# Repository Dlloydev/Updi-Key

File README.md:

# Updi-Key

#### What is it?

Updi-Key is an inline adapter that transforms your favorite UPDI programmer into a HV UPDI programmer.  Now you can easily enable UPDI mode, program and power-cycle your target MCU to explore additional features like using the UPDI pin for LUT0, AIN0, GPIO or Reset.

#### Why did you make it?

To provide a tool that allows easy access to the additional functions of the programming pin, which becomes more important in low pin count applications. To enhance your existing programming solution with a convenient low cost adapter.

#### What makes it special?

Unique, versatile, easy to use with the existing programming environment you're already familiar with.

- Converts any UPDI programmer to HV-UPDI
- Connects directly in-line with the MPLAB Snap In-Circuit Debugger (pins 2, 3, 4)
- Connects directly in-line with many ATtiny 0/1/2 development and breakout boards
- Provides standard 6-pin UPDI headers with pin 3 used for additional functions
- The 3-pin UPDI headers can be any combination of male/female or vertical/horizontal at each end
- Automatically provides target power-cycle with current limiting protection
- Directly compatible with any target voltage from 3V to 5V without reprogramming the device
- Host UPDI is inherently protected by using "break-before-make" signal transfer
- No power hungry resistor-diode host UPDI protection circuit required
- Built-in low noise, low EMI, low power 3-5VDC to 12VDC converter (25mA) 
-  Fast HV pulse timing similar to the Atmel Power Debugger
- Continuously monitors host UPDI signal and Re-Updify button on one pin for detecting stable or busy status of the UPDI signal and pushbutton status 
- Green VTG-PC status LED and Orange HV pulse LED
- It seems fitting that the smallest MCU in the family (ATtiny202) operates the key

#### Updi-Key Digi-Key BOM

| Item | Qty  | Reference   | Manufacturer  Number                                         | Digi-Key Part Number     | Description                                                |
| ---- | ---- | ----------- | ------------------------------------------------------------ | ------------------------ | ---------------------------------------------------------- |
| 1    | 3    | C1, C7, C8  | [CL10B104KB8NNNC](https://www.mouser.ca/datasheet/2/585/MLCC-1837944.pdf) | 1276-1000-1-ND           | CAP CER 0.1UF 50V X7R 0603                                 |
| 2    | 1    | C6          | [CL10A475KO8NNNC](https://media.digikey.com/pdf/Data%20Sheets/Samsung%20PDFs/CL10A475KO8NNNC_Spec.pdf) | 1276-1784-1-ND           | CAP CER 4.7UF 16V X5R 0603                                 |
| 3    | 1    | D2          | [PMEG4005CEJX](https://assets.nexperia.com/documents/data-sheet/PMEG4005CEJ.pdf) | 1727-8169-1-ND           | DIODE SCHOTTKY 40V 500MA SC90                              |
| 4    | 2    | R8, R9      | [RK73B1JTTD102J](http://www.koaspeer.com/pdfs/RK73B.pdf)     | 2019-RK73B1JTTD102JCT-ND | RES 1K OHM 5% 1/8W 0603                                    |
| 5    | 3    | R3, R4, R10 | [RK73B1JTTD103J](http://www.koaspeer.com/pdfs/RK73B.pdf)     | 2019-RK73B1JTTD103JCT-ND | RES 10K OHM 5% 1/10W 0603                                  |
| 6    | 2    | R11, R12    | [RK73B1JTTD181J](http://www.koaspeer.com/pdfs/RK73B.pdf)     | 2019-RK73B1JTTD181JCT-ND | RES 180 OHM 5% 1/8W 0603                                   |
| 7    | 1    | SW1         | [SN74LVC1G3157DBVR](http://www.ti.com/general/docs/suppproductinfo.tsp?distId=10&gotoUrl=http%3A%2F%2Fwww.ti.com%2Flit%2Fgpn%2Fsn74lvc1g3157) | 296-14908-1-ND           | IC SWITCH SPDT SOT23-6                                     |
| 8    | 1    | R6          | [RC0603FR-0711KL](https://www.yageo.com/upload/media/product/productsearch/datasheet/rchip/PYu-RC_Group_51_RoHS_L_11.pdf) | 311-11.0KHRCT-ND         | RES SMD 11K OHM 1% 1/10W 0603                              |
| 9    | 1    | R5          | [RC0603FR-07102KL](https://www.yageo.com/upload/media/product/productsearch/datasheet/rchip/PYu-RC_Group_51_RoHS_L_11.pdf) | 311-102KHRCT-ND          | RES SMD 102K OHM 1% 1/10W 0603                             |
| 10   | 1    | C4          | [CC0603BRNPO9BNR68](https://www.yageo.com/upload/media/product/productsearch/datasheet/mlcc/UPY-GP_NP0_16V-to-50V_18.pdf) | 311-3842-1-ND            | CAP CER 0.68PF 50V NPO 0603                                |
| 11   | 1    | VTG1        | [LG Q396-PS-35](https://dammedia.osram.info/media/resource/hires/osram-dam-2493948/LG%20Q396.pdf) | 475-3754-1-ND            | LED GREEN DIFFUSED 0603 SMD                                |
| 12   | 1    | F1          | [0ZCM0005FF2G](https://belfuse.com/resources/datasheets/circuitprotection/ds-cp-0zcm-series.pdf) | 507-1816-1-ND            | PTC RESET FUSE 15V 50MA 0603                               |
| 13   | 1    | U3          | [MIC2091-1YM5-TR](http://www.microchip.com/mymicrochip/filehandler.aspx?ddocname=en579481) | 576-3891-1-ND            | MICROCHIP - MIC2091-1YM5-TR - POWER SWITCH, 100MA, SOT23-5 |
| 14   | 1    | L1          | [CBC2518T470K](https://www.mouser.ca/datasheet/2/396/wound02_e-13113-1206718.pdf) | 587-3060-1-ND            | FIXED IND 47UH 290MA 2.47 OHM                              |
| 15   | 3    | C2, C3, C5  | [LMK107BBJ106MALT](https://www.mouser.ca/datasheet/2/396/wound02_e-13113-1206718.pdf) | 587-3258-1-ND            | CAP CER 10UF 10V X5R 0603                                  |
| 16   | 1    | HV1         | [APTD1608SECK/J4-PF](https://www.mouser.ca/datasheet/2/216/APTD1608SECK-J4-PF-472092.pdf) | 754-1802-1-ND            | LED ORANGE CLEAR 0603 (1608 Metric)                        |
| 17   | 1    | U1          | [ATTINY202-SSNR](http://ww1.microchip.com/downloads/en/DeviceDoc/ATtiny202-402-AVR-MCU-with-Core-Independent-Peripherals_and-picoPower-40001969A.pdf) | ATTINY202-SSNRCT-ND      | IC MCU 8BIT 2KB FLASH 8SOIC                                |
| 18   | 1    | SW3         | [PTS810SJG250SMTRLFS](https://dznh3ojzb2azq.cloudfront.net/products/Tactile/PTS810/documents/datasheet.pdf) | CKN10504CT-ND            | SWITCH TACTILE SPST-NO 0.05A 16V                           |
| 19   | 1    | SW2         | [ISL43210IHZ-T](https://www.renesas.com/en-us/www/doc/datasheet/isl43210.pdf) | ISL43210IHZCT-ND         | IC SWITCH SPDT SOT23-6, Marking GJQG                       |
| 20   | 1    | U2          | [NCP1406SNT1G](http://www.onsemi.com/pub/Collateral/NCP1406-D.PDF) | NCP1406SNT1GOSCT-ND      | IC REG BUCK BST ADJ 25MA 5TSOP                             |

#### Schematic

#### Firmware Installation

1. Connect a UPDI programmer to J3 (Pin2  VTG to VCC, Pin3 PROG to UPDI, Pin6 to GND)

2. Install the latest version of [megaTinyCore](https://github.com/SpenceKonde/megaTinyCore/blob/master/Installation.md)

3. Install the [Updi-Key Firmware](https://github.com/Dlloydev/Updi-Key) 

   ●  Click on the green "Clone or download" button, then select "Download ZIP".

   ●  Unzip this file in a folder on your PC.

   ●  In the Arduino IDE, open the sketch "UpdiKey.ino" in the "source\updikey" folder

   ●  Use these board settings:

   ●  Select "Burn Bootloader" then "Upload Using Programmer" from the Arduino IDE.  Updi-Key is now ready to use.

#### Functional Description

**High Voltage Programming Options**

| Mode                                | Description                                                  |
| ----------------------------------- | ------------------------------------------------------------ |
| Simple High Voltage Pulse           | On power-up, Updi-Key safely transfers onto the UPDI signal and applies the 12V pulse,  triggers low to initiate the enable sequence then sends the SYNC character and the NVMPROG key, then switches the signal back to the host programmer. The target's PA0 pin remains in UPDI mode as long as power remains on. For additional programming sessions, pressing the Re-updify button is not required. Any changes to the fuses will get loaded on the next power-up. |
| Auto Power Cycle High Voltage Pulse | On power-up, the target's PA0 pin is changed to UPDI mode as described above. After programming, an automatic power-cycle will occur and any new fuse settings will take effect. If re-programming is required, press the Re-updify button first.  This power-cycles and sends the HV pulse and enable sequence to re-activate UPDI mode. |

**UPDI Host Pin Description**

| Pin  | Name      | Type  | Description                   |
| ---- | --------- | ----- | ----------------------------- |
| J2-1 | UPDI-HOST | I/O   | UPDI signal from programmer   |
| J2-2 | GND       | Power | Ground                        |
| J2-3 | VTG       | Power | Target voltage supply (3-5V)  |
|      |           |       |                               |
| J3-1 | UPDI-HOST | I/O   | UPDI signal from programmer   |
| J3-2 | VTG       | Power | Target voltage supply (3-5V)  |
| J3-3 | PROG      | I/O   | Updi-Key UPDI programming pin |
| J3-6 | GND       | Power | Ground                        |

**UPDI Target Pin Description**

| Pin  | Name          | Type  | Description                                                  |
| ---- | ------------- | ----- | ------------------------------------------------------------ |
| J5-1 | HVUPDI-TARGET | I/O   | HVUPDI signal to target                                      |
| J5-2 | GND           | Power | Ground                                                       |
| J5-3 | VTG-PC        | Power | Target voltage supply (3-5V)  with Power Cycle and 100mA current limiting |
|      |               |       |                                                              |
| J4-1 | HVUPDI-TARGET | I/O   | HVUPDI signal to target                                      |
| J4-2 | VTG-PC        | Power | Target voltage supply (3-5V)  with Power Cycle and 100mA current limiting |
| J4-3 | VTG           | I/O   | Target voltage supply (3-5V)                                 |
| J4-6 | GND           | Power | Ground                                                       |

**Green VTG LED:**

This LED is connected to VTG-PC so it will be both power on indication and power-cycle indication.

**Orange HV LED**:

On power-up or just after the Re-Updify button is released, the orange HV LED will be on during the HV pulse and enable sequence.

**Target Power:**

**VTG-PC:**  This pin is the output of the MIC2091 power switch that is optimized for 100mA over-current limiting and circuit protection.

**VTG:**  This pin connects directly to your external power source.

**Re-Updify:**

This button is used just prior to re-programming when using "Auto Power Cycle and High Voltage Pulse" mode.

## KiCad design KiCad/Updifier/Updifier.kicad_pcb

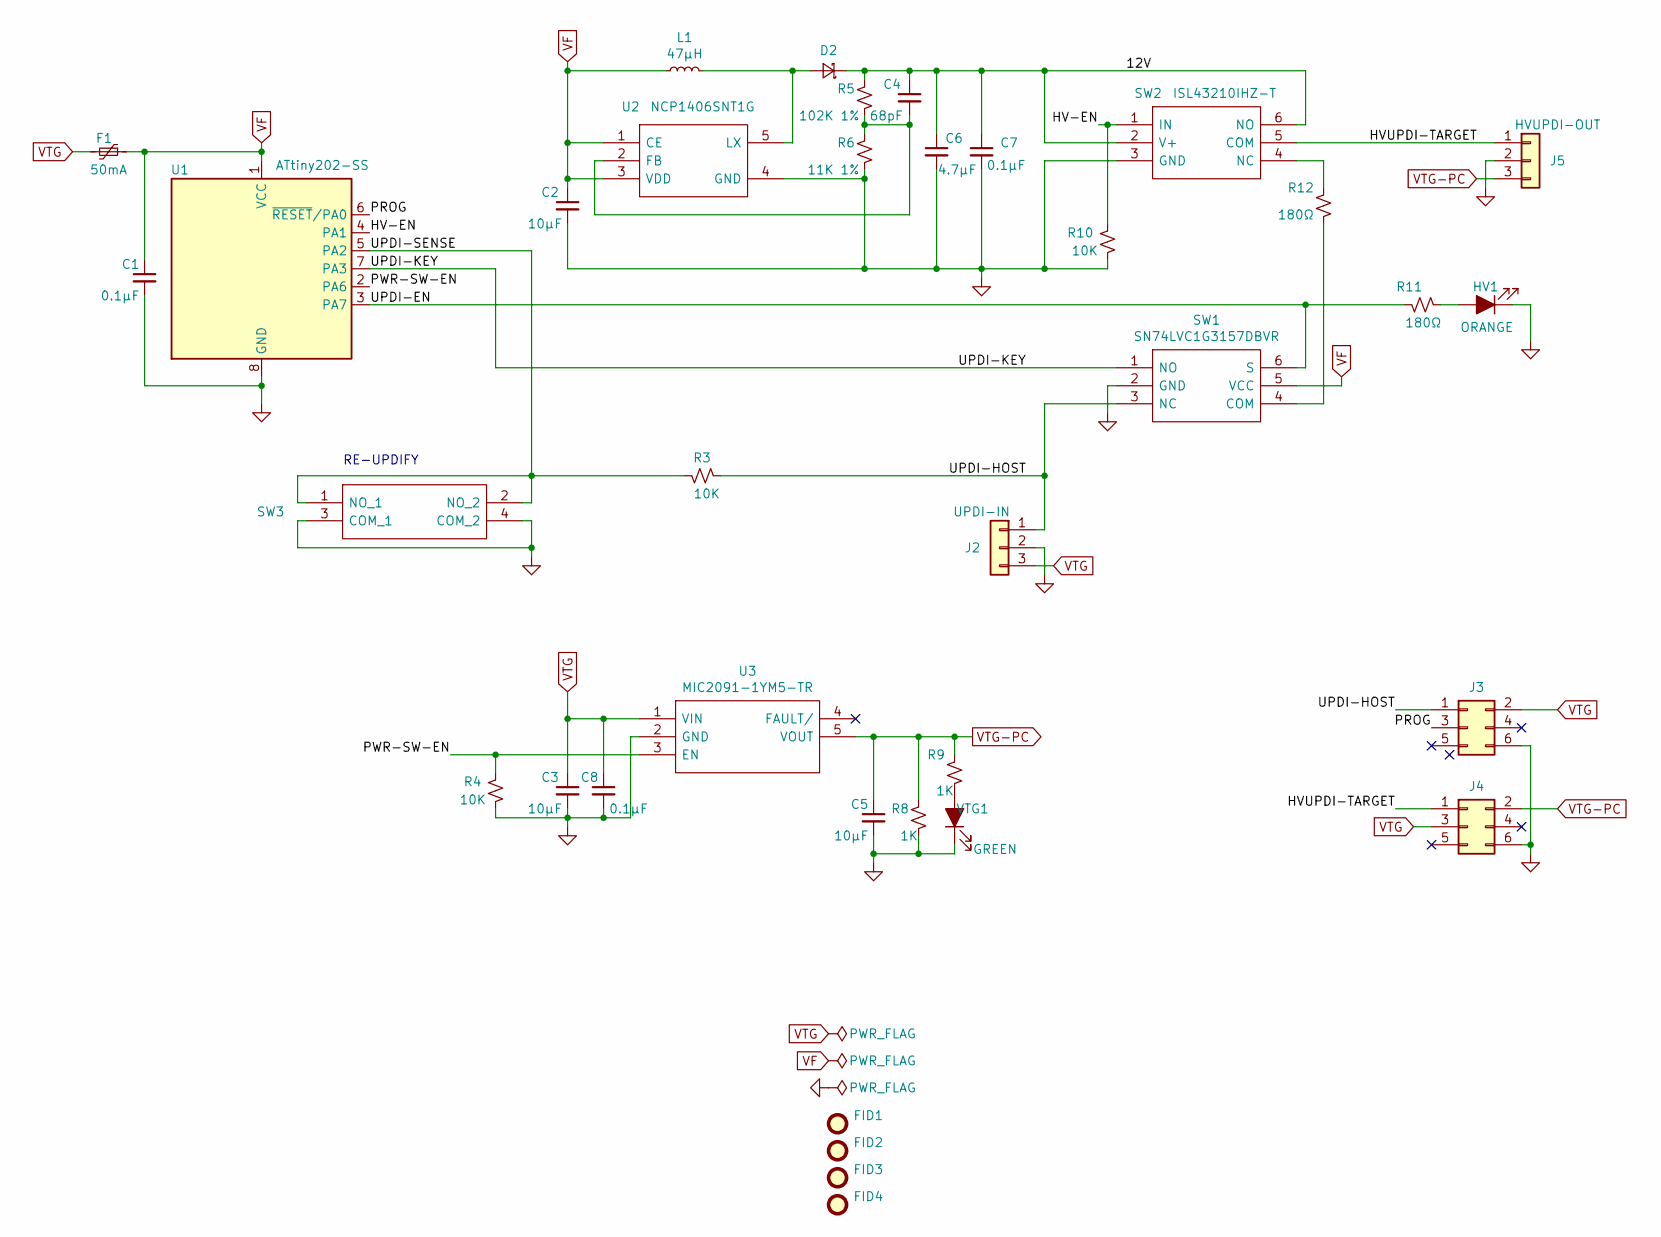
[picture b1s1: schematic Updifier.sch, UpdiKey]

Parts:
C1, C7, C8: 0.1µF; C_0603_1608Metric; Manufacturer_Part_Number CL10B104KB8NNNC; Digi-Key Part Number 1276-1000-1-ND
C2, C3, C5: 10µF; C_0603_1608Metric; Manufacturer_Part_Number LMK107BBJ106MALT; Digi-Key Part Number 587-3258-1-ND
C4: 68pF; C_0603_1608Metric; Manufacturer_Part_Number CC0603BRNPO9BNR68; Digi-Key Part Number 311-3842-1-ND
C6: 4.7µF; C_0603_1608Metric; Manufacturer_Part_Number CL10A475KO8NNNC; Digi-Key Part Number 1276-1784-1-ND
D2: PMEG4005CEJX; D_SOD-323F; Manufacturer_Part_Number PMEG4005CEJX; Digi-Key Part Number 1727-8169-1-ND
F1: 50mA; Fuse_0603_1608Metric; Manufacturer_Part_Number 0ZCM0005FF2G; Digi-Key Part Number 507-1816-1-ND
FID1, FID2, FID3, FID4: Fiducial; Fiducial_1mm_Mask2mm
HV1: ORANGE; LED_0603_1608Metric; Manufacturer_Part_Number APTD1608SECK/J4-PF; Digi-Key Part Number 754-1802-1-ND
J2: UPDI-IN; PinHeader_1x03_P2.54mm_Horizontal
J3: UPDI_IN6; PinHeader_2x03_P2.54mm_Vertical
J4: HVUPDI_OUT6; PinHeader_2x03_P2.54mm_Vertical
J5: HVUPDI-OUT; PinSocket_1x03_P2.54mm_Horizontal
L1: 47µH; L_1008_2520Metric; Manufacturer_Part_Number CBC2518T470K; Digi-Key Part Number 587-3060-1-ND
R3, R4, R10: 10K; R_0603_1608Metric; Manufacturer_Part_Number RK73B1JTTD103J; Digi-Key Part Number 2019-RK73B1JTTD103JCT-ND
R5: 102K 1%; R_0603_1608Metric; Manufacturer_Part_Number RC0603FR-07102KL; Digi-Key Part Number 311-102KHRCT-ND
R6: 11K 1%; R_0603_1608Metric; Manufacturer_Part_Number RC0603FR-0711KL; Digi-Key Part Number 311-11.0KHRCT-ND
R8, R9: 1K; R_0603_1608Metric; Manufacturer_Part_Number RK73B1JTTD102J; Digi-Key Part Number 2019-RK73B1JTTD102JCT-ND
R11, R12: 180Ω; R_0603_1608Metric; Manufacturer_Part_Number RK73B1JTTD181J; Digi-Key Part Number 2019-RK73B1JTTD181JCT-ND
SW1: SN74LVC1G3157DBVR; SOT95P280X145-6N; Manufacturer_Part_Number SN74LVC1G3157DBVR; Mouser Part Number 595-SN74LVC1G3157DBV
SW2: ISL43210IHZ-T; SOT95P280X145-6N; Manufacturer_Part_Number ISL43210IHZ-T; Mouser Part Number 968-ISL43210IHZ-T
SW3: PTS810SJG250SMTRLFS; Manufacturer_Part_Number PTS810SJG250SMTRLFS; Mouser Part Number 611-PTS810SJG250SMTR
U1: ATtiny202-SS; SOIC-8_3.9x4.9mm_P1.27mm; Manufacturer_Part_Number ATTINY202-SSNR; Digi-Key Part Number ATTINY202-SSNRCT-ND
U2: NCP1406SNT1G; SOT95P275X110-5N; Manufacturer_Part_Number NCP1406SNT1G; Mouser Part Number 863-NCP1406SNT1G
U3: MIC2091-1YM5-TR; SOT95P280X130-5N; Manufacturer_Part_Number MIC2091-1YM5-TR; Mouser Part Number 998-MIC2091-1YM5TR
VTG1: GREEN; LED_0603_1608Metric; Manufacturer_Part_Number LG Q396-PS-35; Digi-Key Part Number 475-3754-1-ND

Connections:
/12V: C4.1, C6.1, C7.1, D2.1 (K), R5.1, SW2.2 (V+), SW2.6 (NO)
/HV-EN: R10.1, SW2.1 (IN), U1.4 (PA1)
/HVUPDI-TARGET: J4.1, J5.1, SW2.5 (COM)
/PROG: J3.3, U1.6 (~RESET~/PA0)
/PWR-SW-EN: R4.1, U1.2 (PA6), U3.3 (EN)
/UPDI-EN: R11.2, SW1.6 (S), U1.3 (PA7)
/UPDI-HOST: J2.1, J3.1, R3.2, SW1.3 (NC)
/UPDI-KEY: SW1.1 (NO), U1.7 (PA3)
/UPDI-SENSE: R3.1, SW3.1 (NO_1), SW3.2 (NO_2), U1.5 (PA2)
GND: C1.2, C2.2, C3.2, C5.2, C6.2, C7.2, C8.2, HV1.1 (K), J2.2, J3.6, J4.6, J5.2, R4.2, R6.2, R8.2, R10.2, SW1.2 (GND), SW2.3 (GND), SW3.3 (COM_1), SW3.4 (COM_2), U1.8 (GND), U2.4 (GND), U3.2 (GND), VTG1.1 (K)
unnamed: C4.2, R5.2, R6.1, U2.2 (FB)
unnamed: D2.2 (A), L1.2, U2.5 (LX)
unnamed: HV1.2 (A), R11.1
unnamed: R9.2, VTG1.2 (A)
unnamed: R12.1, SW2.4 (NC)
unnamed: R12.2, SW1.4 (COM)
VF: C1.1, C2.1, F1.1, L1.1, SW1.5 (VCC), U1.1 (VCC), U2.1 (CE), U2.3 (VDD)
VTG: C3.1, C8.1, F1.2, J2.3, J3.2, J4.3, U3.1 (VIN)
VTG-PC: C5.1, J4.2, J5.3, R8.1, R9.1, U3.5 (VOUT)

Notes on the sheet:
RE-UPDIFY

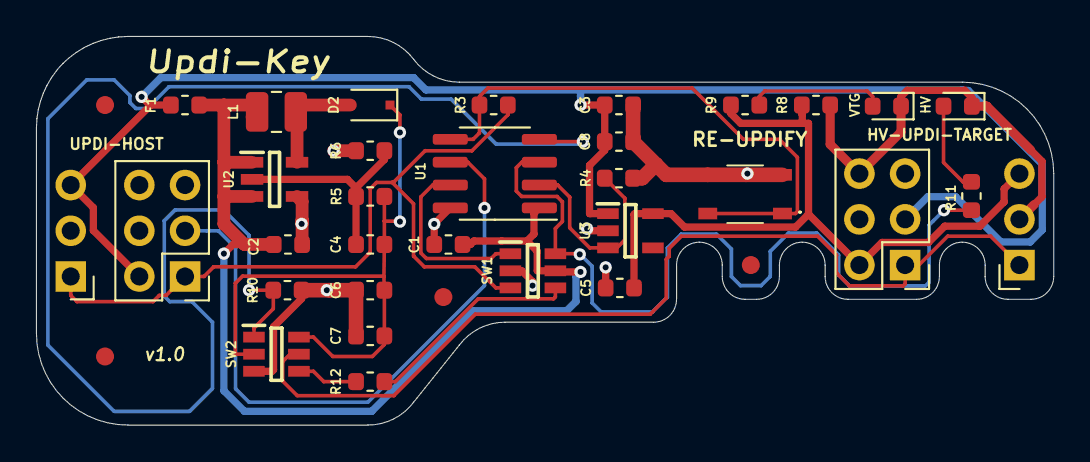
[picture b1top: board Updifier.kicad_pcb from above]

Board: 2 copper layers, 56.5 x 21.6 mm, 36 parts (0 on the bottom side), 19 nets.

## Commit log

2023-10-25 Fix 1k ohm resistor digikey part number
